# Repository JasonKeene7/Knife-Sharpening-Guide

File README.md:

# Knife-Sharpening-Guide
An Arduino based project to assist in keeping a consistent grinding angle.

Having recently finished building, setting up, and toubleshooting my PC, I figured starting a neew project should be my next step. Get to prevent my electronics skills from getting rusty, find all the productivity programs I need to install, and to curb my abject and growing bordem.

On the side, I was also learning my way around the kitchen which of course includes keeping all the knives sharp. Noticed they began dulling, so I took out my grindstone set hoping to rehone the edges; grind, wash, grind, wash, repeat, repeat, paper test… still made the cut, but not as smooth as I hoped and as I already done after a previous session. Huh…. Had a good, disatisfied peer down along the edge, the light just about catch the bevel’s curvature. Go figue I messed up my grinding angle, damn thing is suppoded to be flat….

“Why not make something calculate the angle for you?” rightly spoke the engineer in the back of my mind. “All I needed was to display the tilt of the knife somehow, it will be a fun warmup!”

The project lasted from the April 20th 2021 to the October 11th 2021: total project time 15 days and .72 hours.

Heads up. I am not a good essay writer, so kindly forgive any amature mistakes.

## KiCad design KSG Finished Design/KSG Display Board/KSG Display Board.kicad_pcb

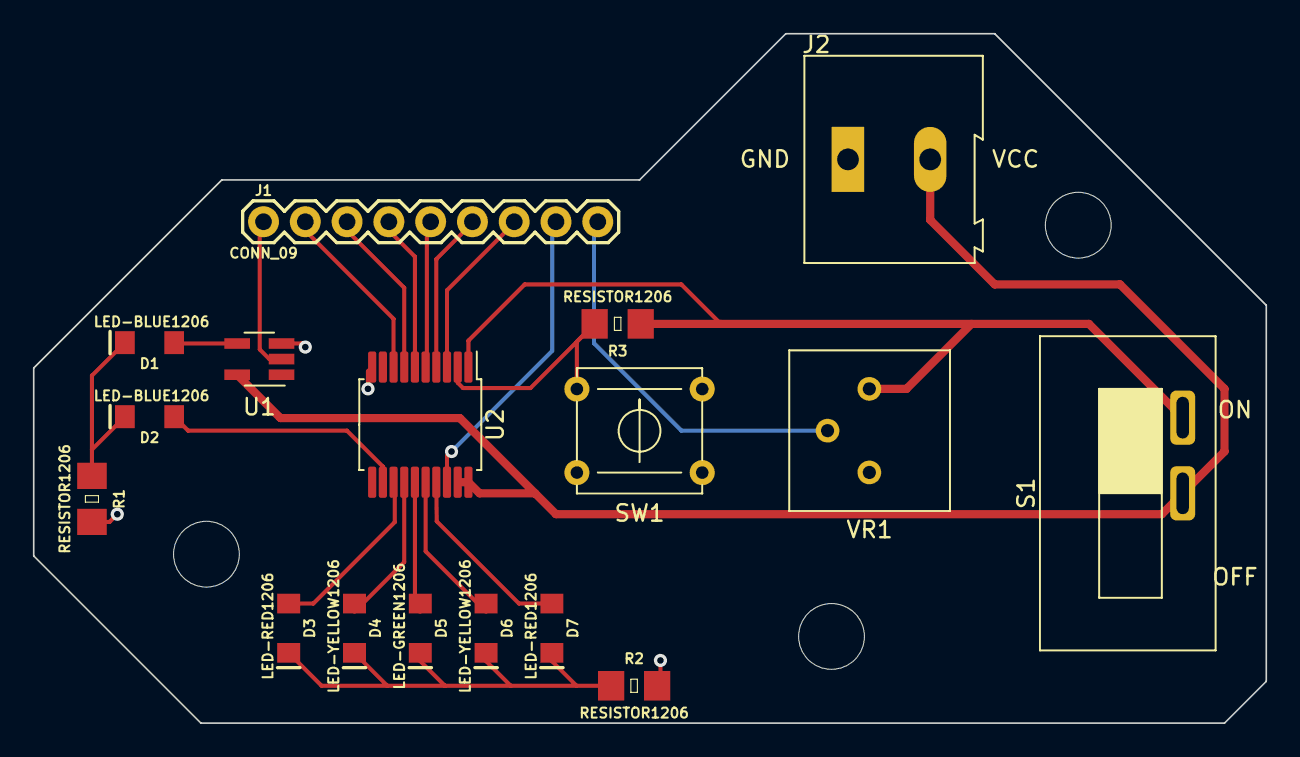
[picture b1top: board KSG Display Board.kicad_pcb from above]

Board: 2 copper layers, 74.9 x 41.9 mm, 17 parts (0 on the bottom side), 22 nets.

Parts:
D1, D2: LED-BLUE1206; LED-1206
D3, D7: LED-RED1206; LED-1206
D4, D6: LED-YELLOW1206; LED-1206
D5: LED-GREEN1206; LED-1206
J1: CONN_09; 1X09
J2: Screw_Terminal_01x02; TerminalBlock_Altech_AK300-2_P5.00mm
R1, R2, R3: RESISTOR1206; 1206
S1: MOMENTARY-SWITCH-SPST-SMD-5.2MM; SPST_Switch_5.08MM
SW1: SW_MEC_5E; General_THT_Pushbutton
U1: 74LVC1G34; SOT-23-5_HandSoldering
U2: 74HCT541; SSOP-20_5.3x7.2mm_P0.65mm
VR1: TRIMPOT-PTH-10MM-KNOB-1_2W-10%; Potentiometer_Bourns_3386P_Vertical

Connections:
5V: J2.2, S1.3, U1.5, U2.19, U2.20
GND: J2.1, R1.2, R2.2, SW1.3, U1.3, U2.10, VR1.3
unnamed: D1.A, U1.4
unnamed: D1.C, D2.C, R1.1
unnamed: D2.A, U2.12
unnamed: D3.A, U2.13
unnamed: D3.C, D4.C, D5.C, D6.C, D7.C, R2.1
unnamed: D4.A, U2.14
unnamed: D5.A, U2.15
unnamed: D6.A, U2.16
unnamed: D7.A, U2.17
unnamed: J1.1, U1.2
unnamed: J1.2, U2.8
unnamed: J1.3, U2.7
unnamed: J1.4, U2.6
unnamed: J1.5, U2.5
unnamed: J1.6, U2.4
unnamed: J1.7, U2.3
unnamed: J1.8, U2.18
unnamed: J1.9, VR1.2
unnamed: R3.1, S1.1, U2.1, VR1.1
unnamed: R3.2, SW1.1, U2.2

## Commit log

2021-10-22 Create Code
2021-10-22 Rename 3DAngleCalc.cpp to Code/3DAngleCalc.cpp
2021-10-22 Rename 3DAngleCalc.h to Code/3DAngleCalc.h
2021-10-22 Rename KSG_Orientation.ino to Code/KSG_Orientation.ino
2021-10-24 Create LICENSE
